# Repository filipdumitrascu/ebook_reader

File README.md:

# Ebook Reader (OpenBook Project)

## Contributor: Dumitrașcu Filip-Teodor 333CA

## 1. Block diagram

## 2. Bill Of Materials (BOM)

| Nume | Component | Link to purchase | Datasheet |
|------|------------|-------------------|-----------|
| PFMF.050.1 | VARISTORCN1812 | [Component Search Engine](https://componentsearchengine.com/part-view/VE1812K401R050/KEMET) | [Datasheet](https://content.kemet.com/datasheets/KEM_V0003_VE.pdf) |
| Rezistente | RR0402 | [Component Search Engine](https://componentsearchengine.com/part-view/R0402%201%25%20100%20K%20(RC0402FR-07100KL)/YAGEO) | [Datasheet](https://content.kemet.com/datasheets/KEM_V0003_VE.pdf)
| J2 | SAMACSYS_PARTS_USB4110-GF-A | [Component Search Engine](https://componentsearchengine.com/part-view/USB4110-GF-A/GCT%20(GLOBAL%20CONNECTOR%20TECHNOLOGY)) | [Datasheet](https://gct.co/files/drawings/usb4110.pdf) |
| D1 | USBLC6-2SC6Y | [Snapeda](https://www.snapeda.com/parts/USBLC6-2SC6Y/STMicroelectronics/view-part/?ref=eda) | [Datasheet](https://www.snapeda.com/parts/USBLC6-2SC6Y/STMicroelectronics/datasheet/) |
| Condensatoare | CC0402 | [Component Search Engine](https://componentsearchengine.com/part-view/CC0402MRX5R5BB106/YAGEO) | [Datasheet](https://componentsearchengine.com/Datasheets/2/CC0402MRX5R5BB106.pdf)|
| Q1 | WROVER_SPARKFUN-DISCRETESEMI_MOSFET_PCH-DMG2305UX-7 | [Component Search Engine](https://componentsearchengine.com/part-view/DMG2305UX-7/Diodes%20Incorporated) | [Datasheet](https://www.diodes.com//assets/Datasheets/DMG2305UX.pdf) |
| D2 | WROVER_AVX---SD0805S020S1R0_AVX_SD0805S020S1R0_0_0AVX_SD0805S020S1R0_0_0 | [Mouser](https://eu.mouser.com/ProductDetail/KYOCERA-AVX/SD0805S020S1R0?qs=jCA%252BPfw4LHbpkAoSnwrdjw%3D%3D) | [Datasheet](https://eu.mouser.com/datasheet/2/40/schottky-3165252.pdf) |
| C3 | RCL_CPOL-EUCT3528 | [Snapeda](https://eu.mouser.com/ProductDetail/KYOCERA-AVX/F910J107MBAAJ6?qs=PqoDHHvF649LraCA%2FjeGXg%3D%3D) | [Datasheet](https://s3.amazonaws.com/snapeda/datasheet/TAJB475K025RNJ_AVX.pdf) |
| J4 | 112A-TAAR-R03_ATTEND | [Snapeda](https://www.snapeda.com/parts/112A-TAAR-R03/Attend/view-part/) | [Datasheet](https://www.snapeda.com/parts/112A-TAAR-R03/Attend/datasheet/) |
| U2 | C6-WROOM-1-N8 | [Snapeda](https://www.snapeda.com/parts/ESP32-C6-WROOM-1-N8/Espressif+Systems/view-part/?ref=eda) | [Datasheet](https://www.snapeda.com/parts/ESP32-C6-WROOM-1-N8/Espressif%20Systems/datasheet/) |
| MCP73831 | WROVER_SPARKFUN-IC-POWER_MCP73831 | [Mouser](https://eu.mouser.com/ProductDetail/Microchip-Technology/MCP73831T-2ACI-OT?qs=yUQqVecv4qvbBQBGbHx0Mw%3D%3D) | [Datasheet](https://eu.mouser.com/datasheet/2/268/MCP73831_Family_Data_Sheet_DS20001984H-3441711.pdf) |
| CHG_LED | ADAFRUIT_LEDCHIP-LED0603 | [Snapeda](https://www.snapeda.com/parts/KP-1608SURCK/Kingbright/view-part/?ref=search&t=LED%200603) | [Datasheet](https://www.snapeda.com/parts/KP-1608SURCK/Kingbright/datasheet/) |
| L1 | 744043680IND_4828-WE-TPC_WRE | [Mouser](https://eu.mouser.com/ProductDetail/Wurth-Elektronik/744043680?qs=PGXP4M47uW6VkZq%252BkzjrHA%3D%3D) | [Datasheet](https://www.we-online.com/components/products/datasheet/744043680.pdf) |
| D3 | MBR0530 | [Snapeda](https://www.snapeda.com/parts/MBR0530/Onsemi/view-part/?ref=eda) | [Datasheet](https://www.snapeda.com/parts/MBR0530/ON%20Semiconductor/datasheet/) |
| Q3 | SI1308EDL-T1-GE3 | [Snapeda](https://www.snapeda.com/parts/SI1308EDL-T1-GE3/Vishay+Siliconix/view-part/?ref=eda) | [Datasheet](https://www.snapeda.com/parts/SI1308EDL-T1-GE3/Vishay+Siliconix/view-part/?ref=eda) |
| SJ1 | SJ | [GrabCad](https://grabcad.com/library/solder-jumpers-1) | [Datasheet](https://www.we-online.com/components/products/datasheet/609002115121.pdf) |
| J1 | FH34SRJ-24S-0.5SH_99_ | [Component Search Engine](https://componentsearchengine.com/part-view/FH34SRJ-24S-0.5SH(99)/Hirose) | [Datasheet](https://www.hirose.com/en/product/document?clcode=CL0580-1255-6-99&productname=FH34SRJ-24S-0.5SH(99)&series=FH34SRJ&documenttype=2DDrawing&lang=en&documentid=0000990903) |
| Sensor2  | WROVER_BME680_BME680 | [Snapeda](https://www.snapeda.com/parts/BME680/Bosch/view-part/?welcome=home) | [Datasheet](https://www.snapeda.com/parts/BME680/Bosch%20Sensortec/datasheet/) |
| Buttons | BUTTON_CUSYOMV1 | [Snapeda](https://www.snapeda.com/parts/EVQP7L01P/Panasonic/view-part/?ref=dk&t=evqp7l01p&con_ref=None) | [Datasheet](https://s3.amazonaws.com/snapeda/datasheet/EVQP7L01P_Panasonic.pdf) |
| U4 | MAX17048G+T10 | [Snapeda](https://www.snapeda.com/parts/MAX17048G+T10/Analog+Devices/view-part/?ref=eda) | [Datasheet](https://www.snapeda.com/parts/MAX17048G+T10/Analog%20Devices/datasheet/) |
| U3 | DS3231SN# | [Snapeda](https://www.snapeda.com/parts/RV-3029-C3-TB-QA-OPT.B/Micro%20Crystal/view-part/?ref=micro%20crystal_rel&p=DS3231SN#&t=None) | [Datasheet](https://www.snapeda.com/parts/DS3231SN%23/Analog%20Devices/datasheet/) |
| C10_SUPERCAP | CPH3225A | [Snapeda](https://www.snapeda.com/parts/CPH3225A/Seiko+Instruments/view-part/?ref=eda) | [Datasheet](https://www.snapeda.com/parts/CPH3225A/Seiko%20Instruments/datasheet/) |
| J3 | QWIIC_CONNECTORJS-1MM | [Snapeda](https://www.snapeda.com/parts/PRT-14417/SparkFun%20Electronics/view-part/?ref=search&t=QWIIC_CONNECTORJS-1MM) | [Datasheet](https://www.snapeda.com/parts/PRT-14417/SparkFun%20Electronics/view-part/?ref=search&t=QWIIC_CONNECTORJS-1MM) |
| D6,8,9,10,11,12 | PGB1010603MR | [Snapeda](https://www.snapeda.com/parts/PGB1010603MR/Littelfuse/view-part/?ref=eda) | [Datasheet](https://www.snapeda.com/parts/PGB1010603MR/Littelfuse%20Inc./datasheet/) |
| U1 | W25Q512JVEIQ | [Snapeda](https://www.snapeda.com/parts/W25Q512JVEIQ/Winbond+Electronics/view-part/?ref=eda) | [Datasheet](https://www.snapeda.com/parts/W25Q512JVEIQ/Winbond%20Electronics/datasheet/) |

## 3. Hardware functionality description

### Components and interfaces
- **ESP32-C6-WROOM-1-N8** is the main microcontroller, responsible for managing the entire system, communicating with sensors and external modules, as well as power management.
  - Architecture: 32-bit RISC-V
  - Operating frequency: 160 MHz
  - Wireless connectivity: Wi-Fi 6 (2.4 GHz), Bluetooth 5.0

- The 3.7V, 1800mAh **Li-Po battery** provides portable power to the system.
- The MCP73831T-based charging circuit manages safe battery charging.
- The LDO regulator stabilizes the supply voltage at 3.3V for all components.

- The 7.5-inch E-Ink display allows information to be displayed with minimal power consumption.
  - Resolution: 800x480 pixels
  - Communication interface: SPI

- **SD Card Module** allows data storage on a MicroSD card (FAT32).
  - Communication interface: SPI

- **External NOR Flash memory** provides 64MB for additional storage.
  - Communication interface: SPI

- **BME688 ambient sensor** measures temperature, humidity, pressure, and gas levels.
  - Communication interface: I2C

- **The DS3231SN RTC module** keeps track of time and date even when the system is turned off.
  - Communication interface: I2C

### Connections and specifications
- **The USB-C connector** allows for system power and data transfer.
  - Integrated ESD protection and Schottky diode for reverse polarity protection.

- **Touch buttons** used for user interaction.

- **Communication interfaces** used:
- GPIO: for buttons and general I/O operations.
  - SPI: for SD Card, NOR Flash memory, and E-Ink display.
  - I2C: for BME688 sensor and RTC module.
  - UART: for debugging and serial communication.
  - Wi-Fi & Bluetooth: provided by ESP32-C6 for wireless connectivity.

## 4. Power Consumption Estimate

| Component                   | Current (mA) | Voltage (V) | Power (mW) |
|-----------------------------|--------------|-------------|------------|
| ESP32-C6 (Wi-Fi active)     | 200          | 3.3         | 660        |
| E-Paper Display (Refresh)   | 40           | 3.3         | 132        |
| BME688 Sensor (Measurement) | 3.1          | 3.3         | 10.23      |
| RTC Module (Active)         | 0.15         | 3.3         | 0.495      |
| SD Card (Active)            | 50           | 3.3         | 165        |
| External NOR Flash Memory   | 25           | 3.3         | 82.5       |

### Estimated Total Consumption
- Total Current: ~318.5 mA  
- Supply Voltage: 3.3 V  
- Total Power: 1050.72 mW

## 5. Pins used on ESP32-C6

| ESP32-C6 Pin | Functionality | Connected Component |
|--------------|----------------|----------------------|
| 3            | EPD_BUSY        | Status signal for EPD (E-paper display) |
| 4            | SS_SD           | Chip Select for SD card |
| 5            | EPD_DC          | Data/Command pin for EPD |
| 6            | SCK             | Common SPI clock line for EPD, SD Card, and external memory |
| 7            | MOSI            | Common SPI MOSI (Master Out Slave In) line for EPD, SD Card, and external memory |
| 2            | MISO            | Common SPI MISO (Master In Slave Out) line for SD Card and external memory |
| 10           | CS_EPD          | Chip Select for EPD |
| 11           | CS_FLASH        | Chip Select for external NOR Flash memory |
| 23           | EPD_RST         | Reset for EPD |
| 21           | SDA             | Common I2C data line for BME688, DS3231 and battery monitoring |
| 22           | SCL             | Common I2C clock line for BME688, DS3231, and battery monitoring |
| 18           | RTC_RST         | Reset for RTC module (DS3231) |
| 1            | 32KHZ           | 32 kHz oscillator for RTC |
| 0            | INT_RTC         | Interrupt signal from RTC |
| 9            | BOOT            | Boot/flash button (user input) |
| 15           | CHANGE          | Button for changing status/functions (user input) |
| EN           | RESET           | General reset button for the system |
| -            | USB-C           | Power supply and programming via USB-C (with ESD protection and Schottky diode) |

## 6. Design aspects and issues encountered
- **Schematic**: Components were positioned according to the system architect's specifications. (I also added frames with names). I accepted 15 warnings when checking the erc
- **PCB 2D**: I split it to get the desired shape in the specifications and placed the components on the edges with the measurements received to ensure that the 3D version fits into the case and the connectors are aligned. I also positioned the central components as in the picture in the specifications. I first autorouted the power nets with a width of 0.3 mm without passing through the bottom plane and then the normal nets of 0.15 with passage through the bottom plane. I placed via stitching near the esp module and the ground planes on both the top and bottom. Indeed, there are a lot of vias placed. Perhaps a better strategy would have been to route the normal nets first so as not to take up space and to place as few vias as possible. Another option would have been to route everything manually. (A bit hardcore for my first project in Fusion 360 with this device, a fairly complex ebook reader). I modified the footprint for parts that had 0.3 mm nets, which were wider than the part pin could support. In the DRC check, I have two approved errors about holes in the footprint of a component. (system architect's mistake)
- **3D PCB**: I downloaded the STEP file and uploaded it for each component so that it would have a 3D representation. The test pads are custom made. I placed the PCB in the case I received from the system architect. I would like to point out that the 15.30mm dimension from the top left corner (with the origin in the bottom left corner) places the SD card below the hole in the case. I chose to move the hole in the case to solve the problem (rather than changing routes, repositioning the SD card, and other 3D pushes).
- **Battery, display**: I made a custom battery and screen (I learned Fusion rather than taking the step file from the internet), noting that the connection wires are missing (a bit much for a first Fusion project). Their dimensions and components are taken from the relevant datasheets.
- **Bom, PcP** I generated the bom, pick and place, and gerbers for the pcb from manufacturing.

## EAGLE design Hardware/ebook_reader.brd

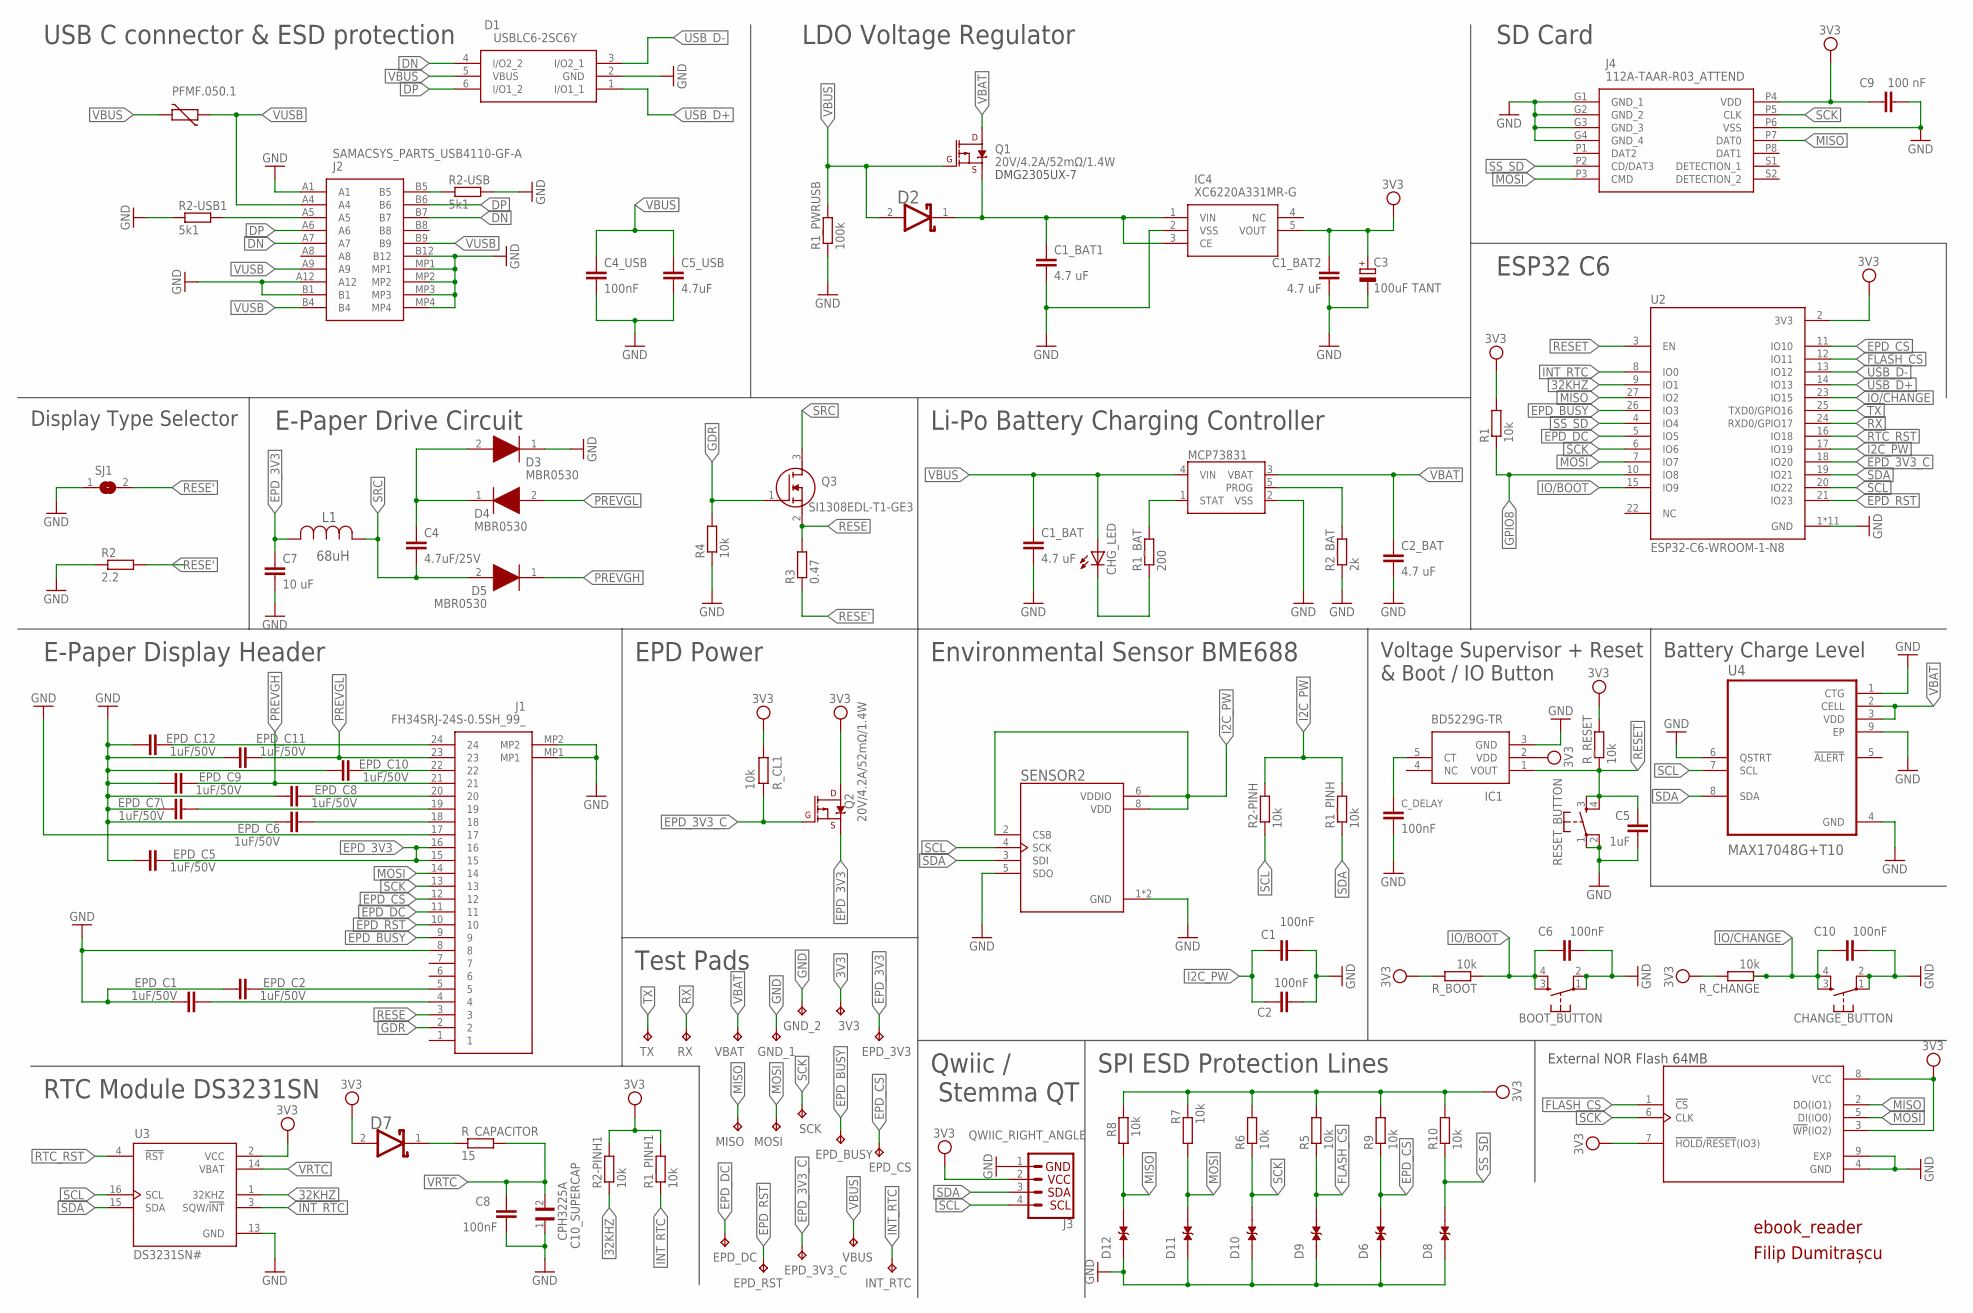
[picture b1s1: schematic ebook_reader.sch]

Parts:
3V3: TPTP20R; TP20R
BOOT_BUTTON: BUTTON_CUSYOMV1; MYBUTTON
C1, C2, C4_USB, C6, C8, C10: 100nF; ESP32_WROVER_EAGLE-LTSPICE_C0402
C1_BAT, C1_BAT1, C1_BAT2, C2_BAT: 4.7 uF; ESP32_WROVER_EAGLE-LTSPICE_C0402
C3: 100uF TANT; RCL_CT3528
C4: 4.7uF/25V; ESP32_WROVER_EAGLE-LTSPICE_C0402
C5: 1uF; ESP32_WROVER_EAGLE-LTSPICE_C0402
C5_USB: 4.7uF; ESP32_WROVER_EAGLE-LTSPICE_C0402
C7: 10 uF; ESP32_WROVER_EAGLE-LTSPICE_C0402
C9: 100 nF; ESP32_WROVER_EAGLE-LTSPICE_C0402
C10_SUPERCAP: CPH3225A; CAPCP3225X100N
CHANGE_BUTTON: BUTTON_CUSYOMV1; MYBUTTON
CHG_LED: ADAFRUIT_LEDCHIP-LED0603; ADAFRUIT_CHIP-LED0603
C_DELAY: 100nF; ESP32_WROVER_EAGLE-LTSPICE_C0402
D1: USBLC6-2SC6Y; SOT95P280X145-6N
D2, D7: ESP32_WROVER_AVX---SD0805S020S1R0_AVX_SD0805S020S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; ESP32_WROVER_AVX---SD0805S020S1R0_AVX_SD0805S020S1R0_0
D3, D4, D5: MBR0530; SOD3716X135N
D6, D8, D9, D10, D11, D12: PGB1010603MR; DIOC1608X36N
EPD_3V3, EPD_3V3_C: TPTP20R; TP20R
EPD_BUSY: TPTP20R; TP20R
EPD_C1, EPD_C2, EPD_C5, EPD_C6, EPD_C7\, EPD_C8, EPD_C9, EPD_C10, EPD_C11, EPD_C12: 1uF/50V; ESP32_WROVER_EAGLE-LTSPICE_C0402
EPD_CS: TPTP20R; TP20R
EPD_DC: TPTP20R; TP20R
EPD_RST: TPTP20R; TP20R
GND_1, GND_2: TPTP20R; TP20R
IC1: BD5229G-TR; SOT95P280X125-5N
IC4: XC6220A331MR-G; SOT95P280X120-5N
INT_RTC: TPTP20R; TP20R
J1: FH34SRJ-24S-0.5SH_99_; FH34SRJ24S05SH99
J2: SAMACSYS_PARTS_USB4110-GF-A; SAMACSYS_PARTS_USB4110GFA
J3: QWIIC_RIGHT_ANGLE; JST04_1MM_RA
J4: 112A-TAAR-R03_ATTEND; 112ATAARR03ATTEND
L1: 68uH; IND_4828-WE-TPC_WRE
MCP73831: ESP32_WROVER_SPARKFUN-IC-POWER_MCP73831; ESP32_WROVER_SPARKFUN-IC-POWER_SOT23-5
MISO: TPTP20R; TP20R
MOSI: TPTP20R; TP20R
PFMF.050.1: ESP32C6_VARISTORCN1812; ESP32C6_VARISTOR_CT/CN1812
Q1, Q2: 20V/4.2A/52mΩ/1.4W; ESP32_WROVER_SPARKFUN-DISCRETESEMI_SOT23-3
Q3: SI1308EDL-T1-GE3; SOT65P210X110-3N
R1, R1_PINH, R1_PINH1, R2-PINH, R2-PINH1, R4, R5, R6, R7, R8, R9, R10: 10k; ESP32_WROVER_EAGLE-LTSPICE_R0402
R1_BAT: 200; ESP32_WROVER_EAGLE-LTSPICE_R0402
R1_PWRUSB: 100k; ESP32_WROVER_EAGLE-LTSPICE_R0402
R2: 2.2; ESP32_WROVER_EAGLE-LTSPICE_R0402
R2-USB, R2-USB1: 5k1; ESP32_WROVER_EAGLE-LTSPICE_R0402
R2_BAT: 2k; ESP32_WROVER_EAGLE-LTSPICE_R0402
R3: 0.47; ESP32_WROVER_EAGLE-LTSPICE_R0402
RESET_BUTTON: BUTTON_CUSYOMV1; MYBUTTON
RX: TPTP20R; TP20R
R_BOOT: 10k; ESP32_WROVER_EAGLE-LTSPICE_R0402
R_CAPACITOR: 15; ESP32_WROVER_EAGLE-LTSPICE_R0402
R_CHANGE: 10k; ESP32_WROVER_EAGLE-LTSPICE_R0402
R_CL1: 10k; ESP32_WROVER_EAGLE-LTSPICE_R0402
R_RESET: 10k; ESP32_WROVER_EAGLE-LTSPICE_R0402
SCK: TPTP20R; TP20R
SENSOR2: ESP32_WROVER_BME680_BME680; ESP32_WROVER_BME680_PSON80P300X300X100-8N
SJ1: SJ
TX: TPTP20R; TP20R
U1: W25Q512JVEIQ; SON127P600X800X80-9N
U2: ESP32-C6-WROOM-1-N8; XCVR_ESP32-C6-WROOM-1-N8
U3: DS3231SN#; SOIC127P1032X265-16N
U4: MAX17048G+T10; SON50P200X200X80-9N
VBAT: TPTP20R; TP20R
VBUS: TPTP20R; TP20R

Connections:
3V3: 3V3.TP, C1_BAT2.1, C3.+, C9.1, D7.2 (ANODE), IC1.2 (VDD), IC4.5 (VOUT), J3.2, J4.P4 (VDD), Q2.3 (D), R1.2, R1_PINH1.2, R2-PINH1.2, R5.2, R6.2, R7.2, R8.2, R9.2, R10.2, R_BOOT.2, R_CHANGE.2, R_CL1.2, R_RESET.2, U1.3 (!WP!(IO2)), U1.7 (!HOLD!/!RESET!(IO3)), U1.8 (VCC), U2.2 (3V3), U3.2 (VCC)
32KHZ: R2-PINH1.1, U2.9 (IO1), U3.1 (32KHZ)
DN: D1.4 (I/O2_2), J2.A7, J2.B7
DP: D1.6 (I/O1_2), J2.A6, J2.B6
EPD_3V3: C7.1, EPD_3V3.TP, EPD_C5.2, J1.15, J1.16, L1.2, Q2.2 (S)
EPD_3V3_C: EPD_3V3_C.TP, Q2.1 (G), R_CL1.1, U2.18 (IO20)
EPD_BUSY: EPD_BUSY.TP, J1.9, U2.26 (IO3)
EPD_CS: D6.2, EPD_CS.TP, J1.12, R9.1, U2.11 (IO10)
EPD_DC: EPD_DC.TP, J1.11, U2.5 (IO5)
EPD_RST: EPD_RST.TP, J1.10, U2.21 (IO23)
FLASH_CS: D9.2, R5.1, U1.1 (!CS), U2.12 (IO11)
GDR: J1.2, Q3.1 (G), R4.2
GND: BOOT_BUTTON.1, BOOT_BUTTON.2, C1.2, C1_BAT.2, C1_BAT1.2, C1_BAT2.2, C2.2, C2_BAT.2, C3.-, C4_USB.2, C5.2, C5_USB.2, C6.2, C7.2, C8.2, C9.2, C10.2, C10_SUPERCAP.1, CHANGE_BUTTON.1, CHANGE_BUTTON.2, C_DELAY.2, D1.2 (GND), D3.1 (K), D6.1, D8.1, D9.1, D10.1, D11.1, D12.1, EPD_C1.1, EPD_C2.1, EPD_C5.1, EPD_C6.1, EPD_C7\.1, EPD_C8.1, EPD_C9.1, EPD_C10.1, EPD_C11.1, EPD_C12.1, GND_1.TP, GND_2.TP, IC1.3 (GND), IC4.2 (VSS), J1.8, J1.17, J1.MP1, J1.MP2, J2.A1, J2.A12, J2.B1, J2.B12, J2.MP1, J2.MP2, J2.MP3, J2.MP4, J3.1, J4.G1 (GND_1), J4.G2 (GND_2), J4.G3 (GND_3), J4.G4 (GND_4), J4.P6 (VSS), MCP73831.2 (VSS), R1_PWRUSB.1, R2.1, R2-USB.2, R2-USB1.1, R2_BAT.1, R4.1, RESET_BUTTON.1, RESET_BUTTON.2, SENSOR2.1 (GND), SENSOR2.5 (SDO), SENSOR2.7 (GND), SJ1.1, U1.4 (GND), U1.9 (EXP), U2.1 (GND), U2.28 (GND), U2.29_1 (GND), U2.29_2 (GND), U2.29_3 (GND), U2.29_4 (GND), U2.29_5 (GND), U2.29_6 (GND), U2.29_7 (GND), U2.29_8 (GND), U2.29_9 (GND), U3.13 (GND), U4.1 (CTG), U4.4 (GND), U4.6 (QSTRT), U4.9 (EP)
GPIO8: R1.1, U2.10 (IO8)
I2C_PW: C1.1, C2.1, R1_PINH.2, R2-PINH.2, SENSOR2.2 (CSB), SENSOR2.6 (VDDIO), SENSOR2.8 (VDD), U2.17 (IO19)
INT_RTC: INT_RTC.TP, R1_PINH1.1, U2.8 (IO0), U3.3 (SQW/!INT)
IO/BOOT: BOOT_BUTTON.3, BOOT_BUTTON.4, C6.1, R_BOOT.1, U2.15 (IO9)
IO/CHANGE: C10.1, CHANGE_BUTTON.3, CHANGE_BUTTON.4, R_CHANGE.1, U2.23 (IO15)
MISO: D12.2, J4.P7 (DAT0), MISO.TP, R8.1, U1.2 (DO(IO1)), U2.27 (IO2)
MOSI: D11.2, J1.14, J4.P3 (CMD), MOSI.TP, R7.1, U1.5 (DI(IO0)), U2.7 (IO7)
unnamed: J2.A5, R2-USB1.2
unnamed: C1_BAT1.1, D2.1 (CATHODE), IC4.1 (VIN), IC4.3 (CE), Q1.2 (S)
unnamed: C4.1, D3.2 (A), D4.1 (K)
unnamed: MCP73831.1 (STAT), R1_BAT.2
unnamed: CHG_LED.C, R1_BAT.1
unnamed: C_DELAY.1, IC1.5 (CT)
unnamed: MCP73831.5 (PROG), R2_BAT.2
unnamed: J2.B5, R2-USB.1
unnamed: EPD_C1.2, J1.4
unnamed: EPD_C2.2, J1.5
unnamed: D7.1 (CATHODE), R_CAPACITOR.1
unnamed: EPD_C6.2, J1.18
unnamed: EPD_C7\.2, J1.19
unnamed: EPD_C8.2, J1.20
unnamed: EPD_C10.2, J1.22
unnamed: EPD_C12.2, J1.24
PREVGH: D5.1 (K), EPD_C9.2, J1.21
PREVGL: D4.2 (A), EPD_C11.2, J1.23
RESE: J1.3, Q3.2 (S), R3.2
RESE': R2.2, R3.1, SJ1.2
RESET: C5.1, IC1.1 (VOUT), RESET_BUTTON.3, RESET_BUTTON.4, R_RESET.1, U2.3 (EN)
RTC_RST: U2.16 (IO18), U3.4 (!RST)
RX: RX.TP, U2.24 (RXD0/GPIO17)
SCK: D10.2, J1.13, J4.P5 (CLK), R6.1, SCK.TP, U1.6 (CLK), U2.6 (IO6)
SCL: J3.4, R2-PINH.1, SENSOR2.4 (SCK), U2.20 (IO22), U3.16 (SCL), U4.7 (SCL)
SDA: J3.3, R1_PINH.1, SENSOR2.3 (SDI), U2.19 (IO21), U3.15 (SDA), U4.8 (SDA)
SRC: C4.2, D5.2 (A), L1.1, Q3.3 (D)
SS_SD: D8.2, J4.P2 (CD/DAT3), R10.1, U2.4 (IO4)
TX: TX.TP, U2.25 (TXD0/GPIO16)
USB_D+: D1.1 (I/O1_1), U2.14 (IO13)
USB_D-: D1.3 (I/O2_1), U2.13 (IO12)
VBAT: C2_BAT.1, MCP73831.3 (VBAT), Q1.3 (D), U4.2 (CELL), U4.3 (VDD), VBAT.TP
VBUS: C1_BAT.1, C4_USB.1, C5_USB.1, CHG_LED.A, D1.5 (VBUS), D2.2 (ANODE), MCP73831.4 (VIN), PFMF.050.1.2, Q1.1 (G), R1_PWRUSB.2, VBUS.TP
VRTC: C8.1, C10_SUPERCAP.2, R_CAPACITOR.2, U3.14 (VBAT)
VUSB: J2.A4, J2.A9, J2.B4, J2.B9, PFMF.050.1.1

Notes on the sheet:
EPD Power
E-Paper Display Header
E-Paper Drive Circuit
Display Type Selector
Li-Po Battery Charging Controller
ESP32 C6
SD Card
LDO Voltage Regulator
USB C connector & ESD protection
Environmental Sensor BME688
Battery Charge Level
Voltage Supervisor + Reset & Boot / IO Button
RTC Module DS3231SN
Test Pads
Qwiic / Stemma QT
SPI ESD Protection Lines
External NOR Flash 64MB
ebook_reader
Filip Dumitrașcu
DMG2305UX-7

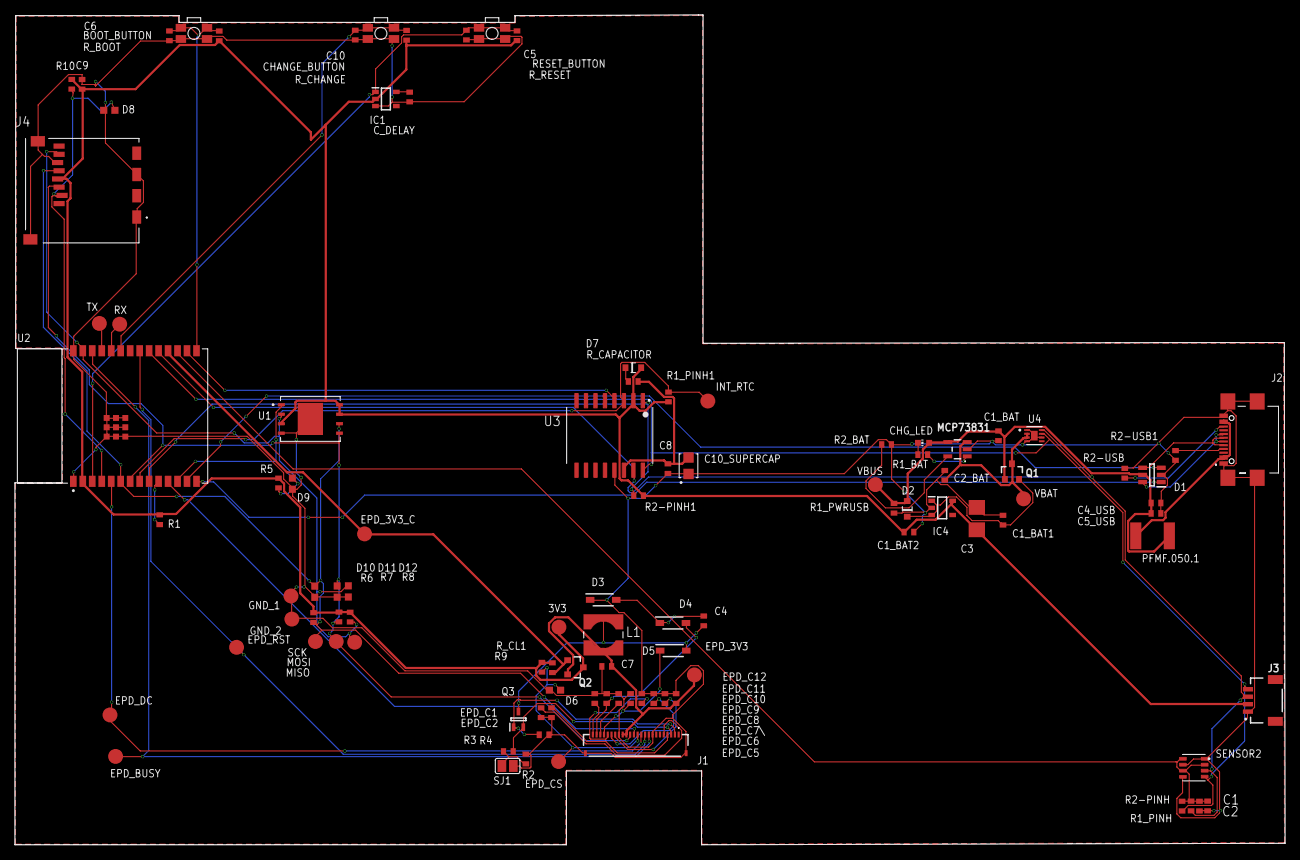
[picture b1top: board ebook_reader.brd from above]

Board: 2 copper layers, 170.2 x 111.2 mm, 103 parts (0 on the bottom side), 55 nets.

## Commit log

2025-04-01 Create LICENSE
2025-04-05 Final version
2025-04-05 File update
2025-04-05 Added diagram
2025-04-05 Readme typo fixed
2025-04-11 Issues fixed

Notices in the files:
parts and their libraries:
COPYRIGHT: Copyright (C) 2024 Ultra Librarian. All rights reserved.
